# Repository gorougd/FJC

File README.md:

# FJC
Collection of radiation detectors, including GM-Tube Driver, and Si-PIN

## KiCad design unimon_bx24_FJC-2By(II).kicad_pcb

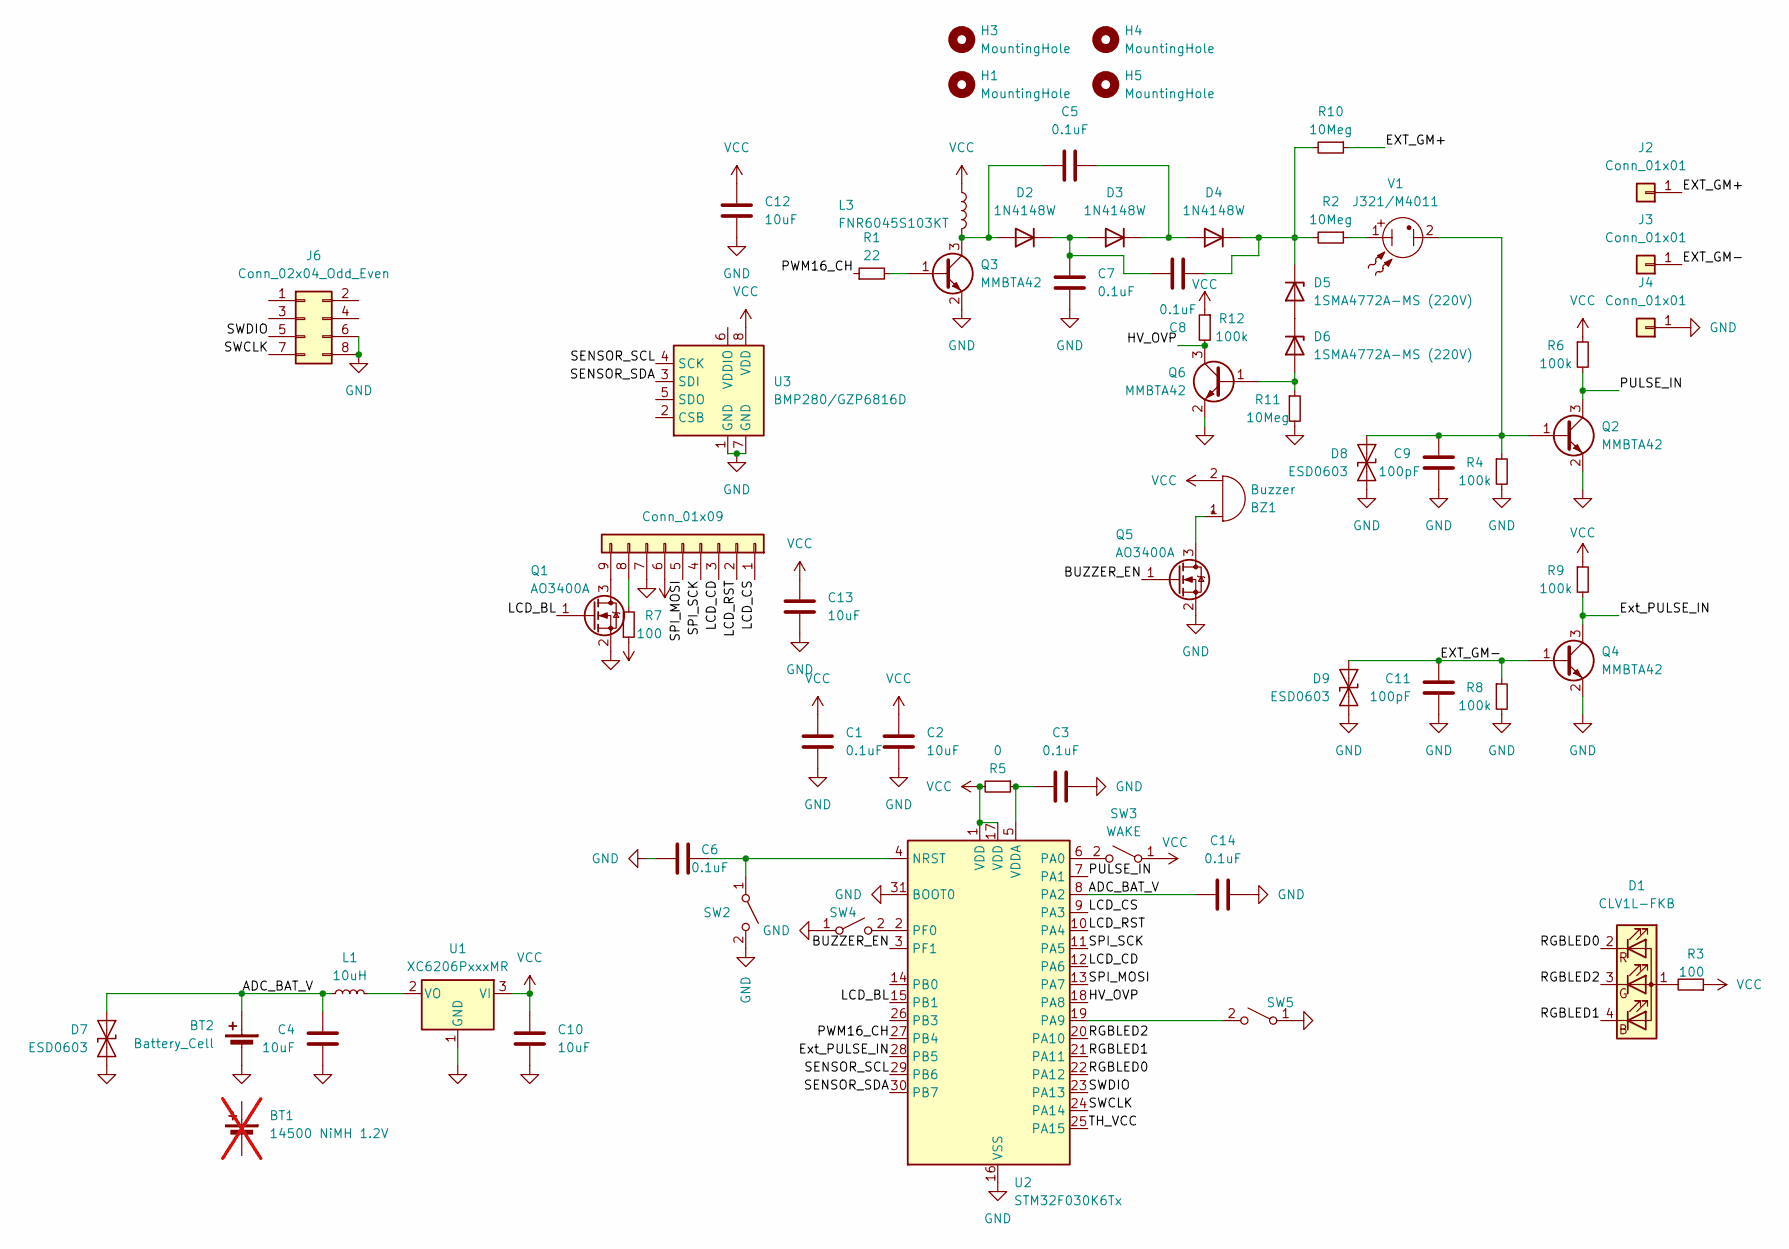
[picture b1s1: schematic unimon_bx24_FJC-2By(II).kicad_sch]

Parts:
BT1: 14500 NiMH 1.2V; 14500_THT_Battery; not fitted
BT2: Battery_Cell; AA_BatHeld_SMD
BZ1: Buzzer; MagneticBuzzer_Kobitone_254-EMB84Q-RO
C1, C3, C6, C14: 0.1uF; C_0603_1608Metric
C2, C4, C10, C12, C13: 10uF; C_0805_2012Metric
C5, C7, C8: 0.1uF; C_1206_3216Metric
C9, C11: 100pF; C_0603_1608Metric
D1: CLV1L-FKB; LED_Cree-PLCC4_3.2x2.8mm_CCW
D2, D3, D4: 1N4148W; D_SOD-123
D5, D6: 1SMA4772A-MS (220V); D_SMA
D7, D8, D9: ESD0603; D_0603_1608Metric
H1, H3, H4, H5: MountingHole; MountingHole_3.5mm
J1: Conn_01x09; FPC_LCD_9pin
J2, J3, J4: Conn_01x01; SolderWire-0.15sqmm_1x01_D0.5mm_OD1.5mm
J6: Conn_02x04_Odd_Even; PinHeader_2x04_P2.54mm_Vertical
L1: 10uH; L_1008_2520Metric
L3: FNR6045S103KT; L_Changjiang_FNR6045S
Q1, Q5: AO3400A; SOT-23
Q2, Q3, Q4, Q6: MMBTA42; SOT-23
R1: 22; R_0603_1608Metric
R2, R10, R11: 10Meg; R_0603_1608Metric
R3, R7: 100; R_0603_1608Metric
R4, R6, R8, R9, R12: 100k; R_0603_1608Metric
R5: 0; R_0603_1608Metric
SW2: SW_SPST; BTN_OVAL_4.2x3.2x2.5
SW3: WAKE; SW_SPST_PTS645
SW4: SW_SPST; SW_SPST_PTS645
SW5: BACKLIGHT; SW_SPST_PTS645
U1: XC6206PxxxMR; SOT-23-3
U2: STM32F030K6Tx; LQFP-32_7x7mm_P0.8mm
U3: BMP280/GZP6816D; Bosch_LGA-8_2x2.5mm_P0.65mm_ClockwisePinNumbering
V1: J321/M4011; J321-M4011_GM_Clip

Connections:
/ADC_BAT_V: BT2.1 (+), C4.1, C14.2, D7.1 (A1), L1.1, U2.8 (PA2)
/BUZZER_EN: Q5.1 (G), U2.3 (PF1)
/EXT_GM+: J2.1, R10.1
/EXT_GM-: C11.2, D9.1 (A1), J3.1, Q4.1 (B), R8.1
/Ext_PULSE_IN: Q4.3 (C), R9.2, U2.28 (PB5)
/HV_OVP: Q6.3 (C), R12.2, U2.18 (PA8)
/LCD_BL: Q1.1 (G), U2.15 (PB1)
/LCD_CD: J1.3, U2.12 (PA6)
/LCD_CS: J1.1, U2.9 (PA3)
/LCD_RST: J1.2, U2.10 (PA4)
/PULSE_IN: Q2.3 (C), R6.2, U2.7 (PA1)
/PWM16_CH: R1.1, U2.27 (PB4)
/RGBLED0: D1.2 (RK), U2.22 (PA12)
/RGBLED1: D1.4 (BK), U2.21 (PA11)
/RGBLED2: D1.3 (GK), U2.20 (PA10)
/SENSOR_SCL: U2.29 (PB6), U3.4 (SCK)
/SENSOR_SDA: U2.30 (PB7), U3.3 (SDI)
/SPI_MOSI: J1.5, U2.13 (PA7)
/SPI_SCK: J1.4, U2.11 (PA5)
/SWCLK: J6.7, U2.24 (PA14)
/SWDIO: J6.5, U2.23 (PA13)
/TH_VCC: U2.25 (PA15)
GND: BT2.2 (-), C1.1, C2.2, C3.1, C4.2, C6.2, C7.1, C9.1, C10.2, C11.1, C12.2, C13.2, C14.1, D7.2 (A2), D8.2 (A2), D9.2 (A2), J1.7, J4.1, J6.6, J6.8, Q1.2 (S), Q2.2 (E), Q3.2 (E), Q4.2 (E), Q5.2 (S), Q6.2 (E), R4.2, R8.2, R11.2, SW2.2 (B), SW4.1 (A), SW5.1 (A), U1.1 (GND), U2.16 (VSS), U2.31 (BOOT0), U2.32 (VSS), U3.1 (GND), U3.7 (GND)
unnamed: BZ1.1 (+), Q5.3 (D)
unnamed: D1.1 (A), R3.2
unnamed: C5.2, D2.2 (A), L3.2, Q3.3 (C)
unnamed: C7.2, C8.1, D2.1 (K), D3.2 (A)
unnamed: C5.1, D3.1 (K), D4.2 (A)
unnamed: C8.2, D4.1 (K), D5.1 (K), R2.2, R10.2
unnamed: D5.2 (A), D6.1 (K)
unnamed: D6.2 (A), Q6.1 (B), R11.1
unnamed: C9.2, D8.1 (A1), Q2.1 (B), R4.1, V1.2
unnamed: J1.8, R7.2
unnamed: J1.9, Q1.3 (D)
unnamed: Q3.1 (B), R1.2
unnamed: R2.1, V1.1
unnamed: C6.1, SW2.1 (A), U2.4 (NRST)
unnamed: SW3.2 (B), U2.6 (PA0)
unnamed: SW4.2 (B), U2.2 (PF0)
unnamed: SW5.2 (B), U2.19 (PA9)
unnamed: L1.2, U1.2 (VO)
unnamed: C3.2, R5.1, U2.5 (VDDA)
VCC: BZ1.2 (-), C1.2, C2.1, C10.1, C12.1, C13.1, J1.6, L3.1, R3.1, R5.2, R6.1, R7.1, R9.1, R12.1, SW3.1 (A), U1.3 (VI), U2.1 (VDD), U2.17 (VDD), U3.8 (VDD)

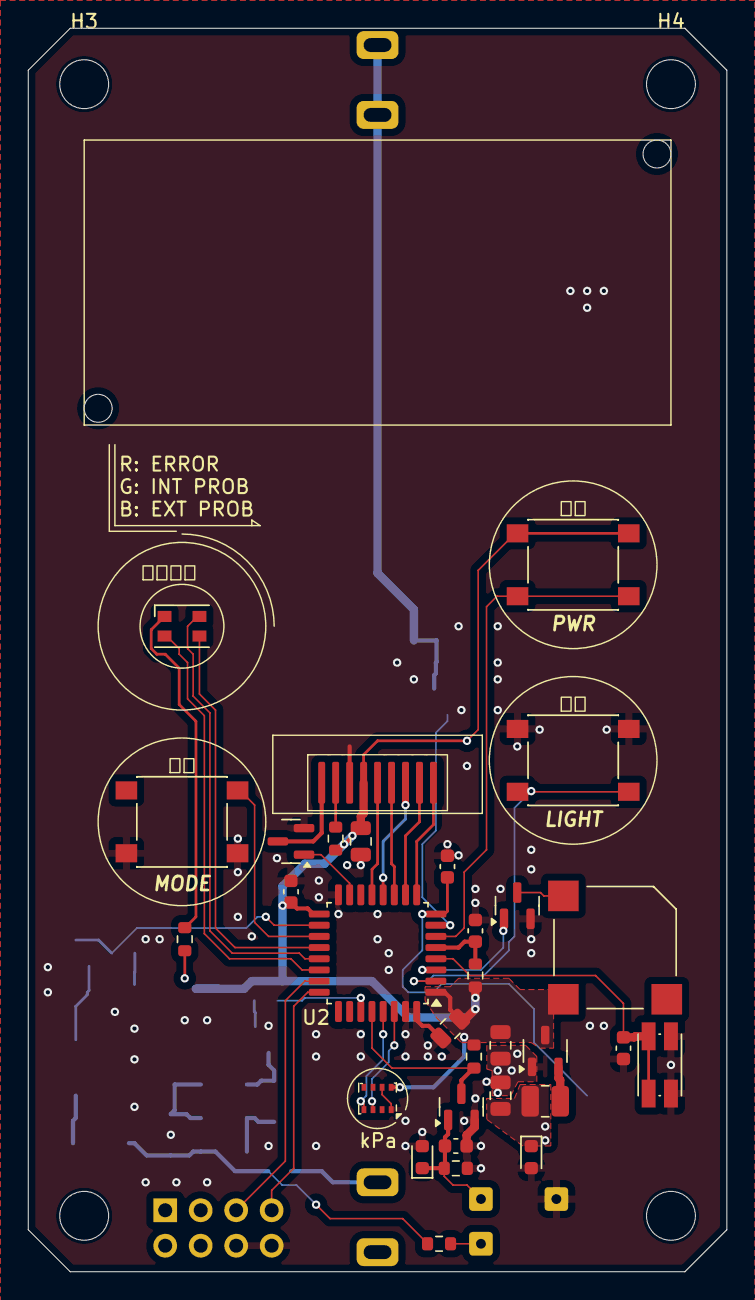
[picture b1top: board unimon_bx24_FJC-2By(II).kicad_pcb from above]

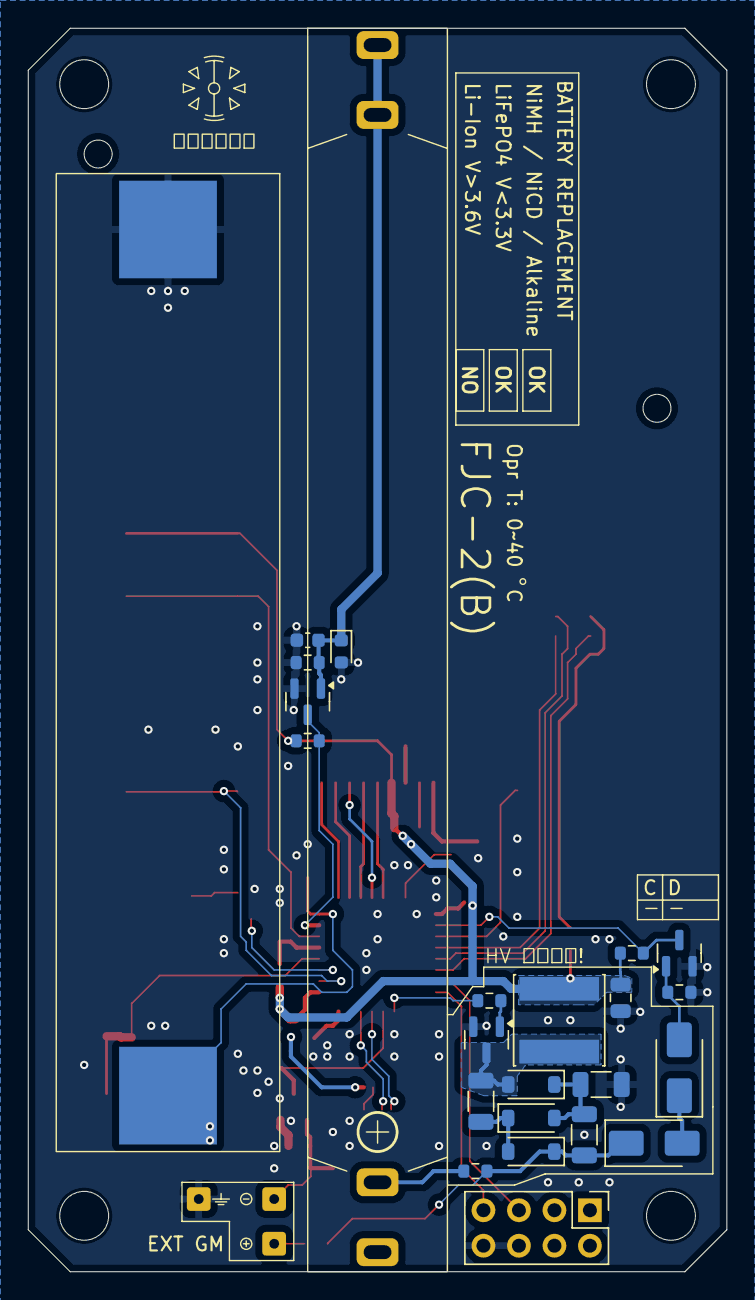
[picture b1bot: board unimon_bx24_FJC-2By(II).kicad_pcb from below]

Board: 2 copper layers, 50.0 x 89.0 mm, 62 parts (24 on the bottom side), 42 nets.

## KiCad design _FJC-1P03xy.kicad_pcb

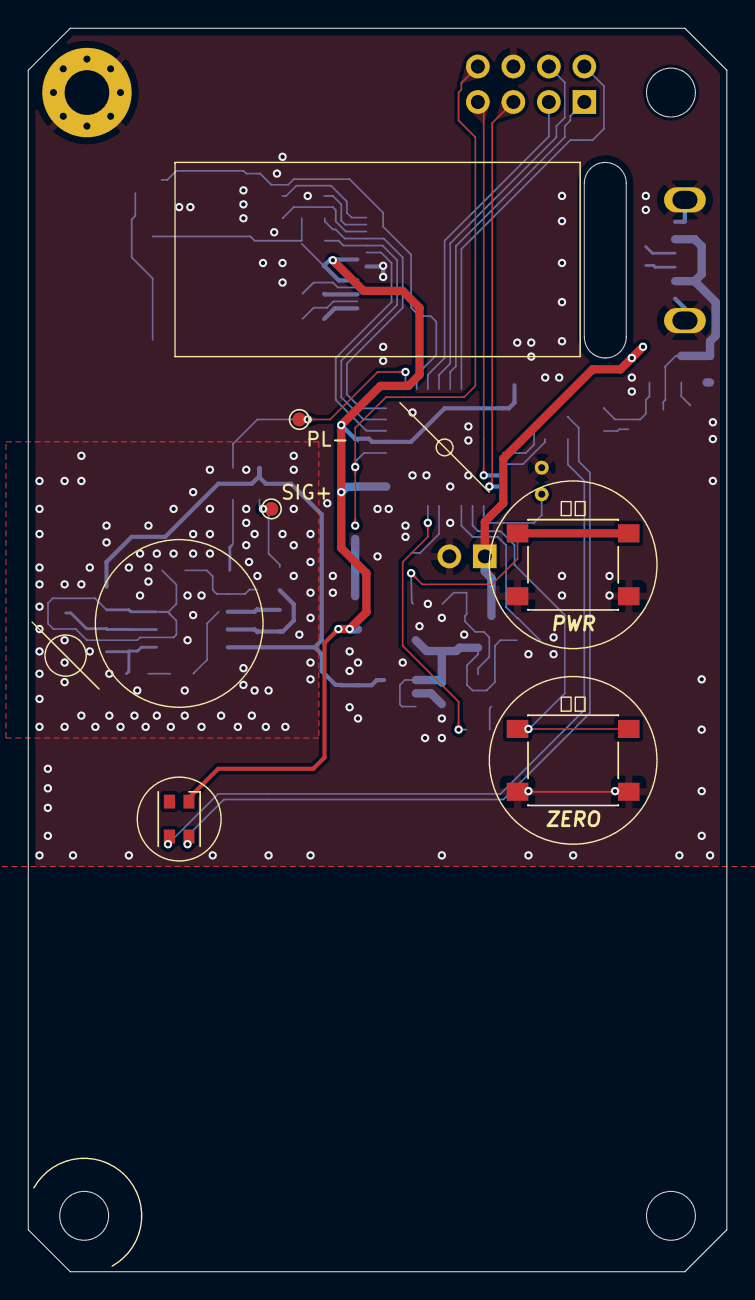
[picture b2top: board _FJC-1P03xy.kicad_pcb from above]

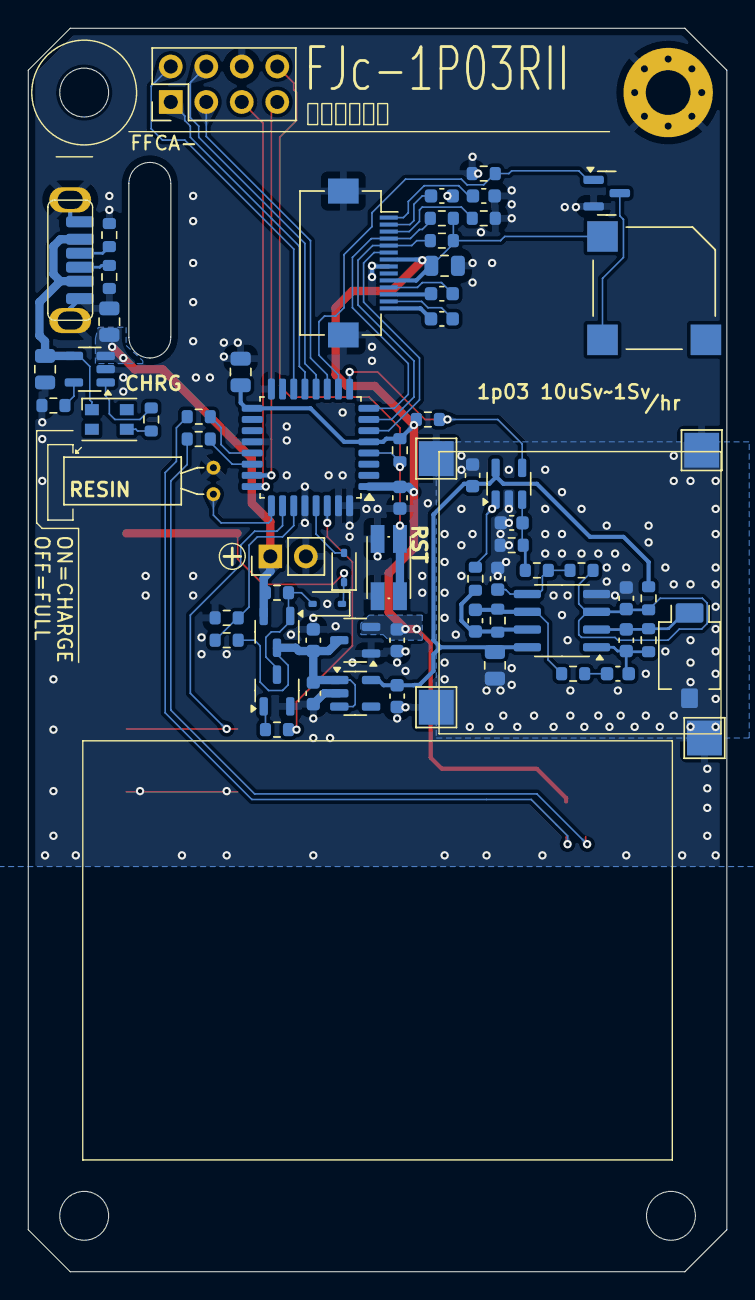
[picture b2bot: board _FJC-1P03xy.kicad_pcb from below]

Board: 2 copper layers, 50.0 x 89.0 mm, 78 parts (69 on the bottom side), 52 nets.

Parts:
BT2: Li; PinHeader_1x02_P2.54mm_Vertical
BZ1: Buzzer; MagneticBuzzer_Kobitone_254-EMB84Q-RO
C1, C17: 0.1uF; C_0603_1608Metric
C2, C8, C11, C20, C21: 10uF; C_0805_2012Metric
C3: 1pF; C_0603_1608Metric
C4, C5, C6, C7, C9, C13, C14, C15, C16, C18, C19: 1uF; C_0603_1608Metric
C10: 100nF; C_0603_1608Metric
C12: 100pF; C_0603_1608Metric
D1: BPW34-SMD; Osram_BPW34S-SMD
D2, D3: 1N4148WS; D_SOD-323
D4, D5: CLV1L-FKB; LED_Cree-PLCC4_3.2x2.8mm_CCW
H2: M3; MountingHole_3.2mm_M3_Pad_Via
H3, H4, H5: MountingHole; MountingHole_3.5mm
J1, J3, J4, J5: Conn_01x01; TestPoint_Pad_2.5x2.5mm
J2: Conn_01x14_MountingPin; Hirose_FH12-14S-0.5SH_1x14-1MP_P0.50mm_Horizontal
J6: Conn_02x04_Odd_Even; PinHeader_2x04_P2.54mm_Vertical
J7: USB_C_Receptacle_PowerOnly_6P; USB_C_top_6pin
Q2: AO3401A; SOT-23-3
Q3: 2N7002; SOT-23-3
Q5: AO3400A; SOT-23
R1, R13, R14: 100; R_0603_1608Metric
R2, R4, R5, R6, R8, R9, R10, R16, R19, R20, R25: 10k; R_0603_1608Metric
R3: 10Meg; R_0603_1608Metric
R7: 510k; R_0603_1608Metric
R11, R15, R17: 100k; R_0603_1608Metric
R12, R18: 1k; R_0603_1608Metric
R22, R23: 5.1k; R_0603_1608Metric
R24: 2.2k; R_0603_1608Metric
SW1: ZERO; SW_SPST_PTS645
SW2: SW_SPST; BTN_OVAL_4.2x3.2x2.5
SW3: WAKE; SW_SPST_PTS645
TP1, TP2: TestPoint; TestPoint_Pad_D1.0mm
U2: LM358; SOIC-8_3.9x4.9mm_P1.27mm
U3: LMV331; SOT-23-5
U4: LP5907MFX-3.0; SOT-23-5
U5: LGS4084H; TSOT-23-5
U6: XC6206PxxxMR; SOT-23-3
U7: STM32F030K6Tx; LQFP-32_7x7mm_P0.8mm
Y1: VIB; Crystal_C38-LF_D3.0mm_L8.0mm_Horizontal

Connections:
+BATT: BT2.1 (+), C21.1, Q2.2 (S), R1.2, U5.3 (BAT)
/BATLV_ADC: R5.2, R6.1, U7.27 (PB4)
/BUZZER_EN: Q5.1 (G), R20.2, U7.10 (PA4)
/LED_MG: R14.2, U7.21 (PA11)
/LED_MR: R13.2, U7.22 (PA12)
/MCU_NRST: J6.8, R4.1, SW2.1 (A), U7.4 (NRST)
/PWR_BTN: D3.2 (A), U7.29 (PB6)
/PWR_ON_LATCH: R2.2, U7.30 (PB7)
/RST_OLED: J2.6, U7.6 (PA0)
/SCL_OLED: J2.5, R8.2, U7.7 (PA1)
/SDA_OLED: J2.4, R9.2, U7.8 (PA2)
/SWCLK: J6.5, U7.24 (PA14)
/SWDIO: J6.7, U7.23 (PA13)
/SW_ZERO: SW1.1 (A), U7.26 (PB3)
/UIO0: J6.3, U7.11 (PA5)
/UIO1: J6.4, U7.12 (PA6)
/UIO2: J6.1, U7.13 (PA7)
/UIO3: J6.2, U7.14 (PB0)
/VBUS: C20.1, D5.1 (A), J7.A9 (VBUS), J7.B9 (VBUS), U5.4 (V_{CC})
/VIBN_OUT: U7.25 (PA15), Y1.2
/V_DEBUG: C15.1, C19.1, Q2.3 (D), R5.1, U4.1 (IN), U4.3 (EN), U6.3 (VI)
/Y_OUT: R19.1, TP2.1, U3.4, U7.9 (PA3)
GND: BT2.2 (-), C1.1, C2.2, C4.2, C5.2, C8.2, C9.2, C11.2, C13.2, C14.2, C15.2, C16.2, C17.1, C18.2, C19.2, C20.2, C21.2, D1.2 (A), H2.1, J1.1, J2.8, J2.MP (MountPin), J3.1, J4.1, J5.1, J6.6, J7.A12 (GND), J7.B12 (GND), J7.S1 (SHIELD), Q3.2 (S), Q5.2 (S), R6.2, R7.2, R17.2, R20.1, R22.1, R23.1, R24.1, SW1.2 (B), SW2.2 (B), SW3.2 (B), U2.4 (V-), U3.2 (V-), U4.2 (GND), U5.2 (GND), U6.1 (GND), U7.16 (VSS), U7.20 (PA10), U7.28 (PB5), U7.31 (BOOT0), U7.32 (VSS), Y1.1
unnamed: BZ1.2 (-), Q5.3 (D)
unnamed: C3.2, C10.1, R3.1, U2.1
unnamed: C10.2, R12.1
unnamed: C12.2, R15.2, R18.1, U2.7
unnamed: C3.1, D1.1 (K), R3.2, U2.2 (-)
unnamed: D2.2 (A), Q2.1 (G), Q3.3 (D), R1.1
unnamed: D2.1 (K), D3.1 (K), SW3.1 (A)
unnamed: D4.4 (BK), R14.1
unnamed: D4.3 (GK), R13.1
unnamed: D5.3 (GK), R25.2
unnamed: C4.1, J2.1
unnamed: C5.1, J2.2
unnamed: J2.3, R7.1
unnamed: C7.2, J2.11
unnamed: C7.1, J2.12
unnamed: C6.2, J2.13
unnamed: C6.1, J2.14
unnamed: J7.A5 (CC1), R23.2
unnamed: J7.B5 (CC2), R22.2
unnamed: Q3.1 (G), R2.1
unnamed: C9.1, R10.2, R11.1, U2.3 (+)
unnamed: C13.1, R11.2, R16.1, U2.5 (+)
unnamed: C12.1, R12.2, R15.1, U2.6 (-)
unnamed: R18.2, TP1.1, U3.1 (+)
unnamed: C14.1, R16.2, R17.1, U3.3 (-)
unnamed: R24.2, U5.5 (STDBY)
unnamed: R25.1, U5.1 (~CHRG)
VCC: BZ1.1 (+), C1.2, C2.1, C8.1, C18.1, D4.1 (A), J2.7, J2.10, R4.2, R8.1, R9.1, R19.2, U6.2 (VO), U7.1 (VDD), U7.5 (VDDA), U7.17 (VDD)
VDDA: C11.1, C16.1, C17.2, R10.1, U2.8 (V+), U3.5 (V+), U4.5 (OUT)

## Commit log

2024-09-29 initial
